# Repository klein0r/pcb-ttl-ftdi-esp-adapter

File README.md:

# TTL over RJ10 to FTDI/ESP12 PCB

[Gerber-Files](https://github.com/klein0r/pcb-ttl-ftdi-esp-adapter/releases)

## Preview

## License

The MIT License (MIT)

Copyright (c) 2026 Matthias Kleine <info@haus-automatisierung.com>

Permission is hereby granted, free of charge, to any person obtaining a copy
of this software and associated documentation files (the "Software"), to deal
in the Software without restriction, including without limitation the rights
to use, copy, modify, merge, publish, distribute, sublicense, and/or sell
copies of the Software, and to permit persons to whom the Software is
furnished to do so, subject to the following conditions:

The above copyright notice and this permission notice shall be included in
all copies or substantial portions of the Software.

THE SOFTWARE IS PROVIDED "AS IS", WITHOUT WARRANTY OF ANY KIND, EXPRESS OR
IMPLIED, INCLUDING BUT NOT LIMITED TO THE WARRANTIES OF MERCHANTABILITY,
FITNESS FOR A PARTICULAR PURPOSE AND NONINFRINGEMENT. IN NO EVENT SHALL THE
AUTHORS OR COPYRIGHT HOLDERS BE LIABLE FOR ANY CLAIM, DAMAGES OR OTHER
LIABILITY, WHETHER IN AN ACTION OF CONTRACT, TORT OR OTHERWISE, ARISING FROM,
OUT OF OR IN CONNECTION WITH THE SOFTWARE OR THE USE OR OTHER DEALINGS IN
THE SOFTWARE.

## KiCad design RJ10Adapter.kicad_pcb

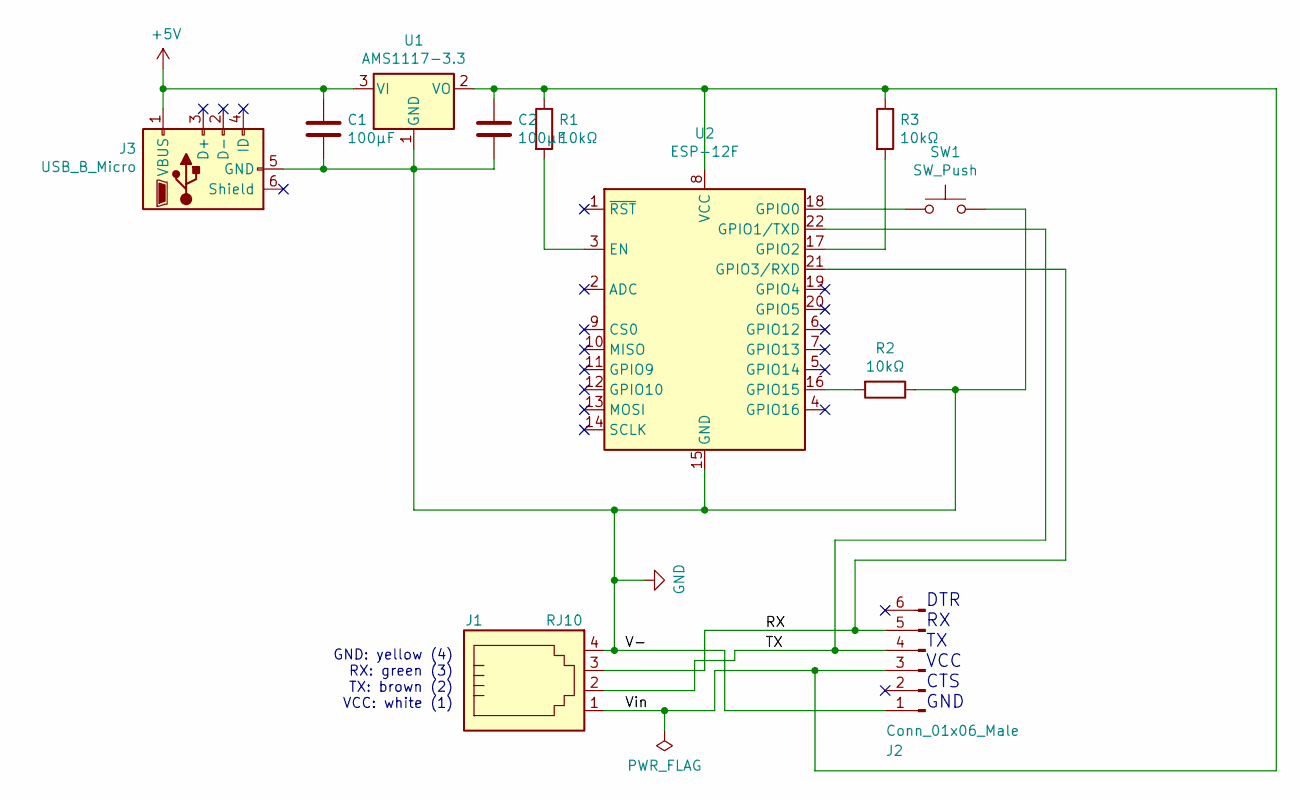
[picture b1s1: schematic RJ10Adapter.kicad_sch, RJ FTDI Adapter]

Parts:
C1, C2: 100µF; C_0805_2012Metric_Pad1.18x1.45mm_HandSolder
J1: RJ10; MEBP_44S
J2: Conn_01x06_Male; PinHeader_1x06_P2.54mm_Vertical
J3: USB_B_Micro; USB_Micro-B_Molex_47346-0001
R1, R2, R3: 10kΩ; R_0805_2012Metric_Pad1.20x1.40mm_HandSolder
SW1: SW_Push; SW_SPST_CK_RS282G05A3
U1: AMS1117-3.3; SOT-223-3_TabPin2
U2: ESP-12F; ESP-12E

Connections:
+5V: C1.1, J3.1 (VBUS), U1.3 (VI)
/RX: J1.3, J2.5, U2.21 (GPIO3/RXD)
/TX: J1.2, J2.4, U2.22 (GPIO1/TXD)
/Vin: C2.1, J1.1, J2.3, R1.1, R3.1, U1.2 (VO), U2.8 (VCC)
GND: C1.2, C2.2, J1.4, J2.1, J3.5 (GND), R2.1, SW1.2, U1.1 (GND), U2.15 (GND)
unnamed: R1.2, U2.3 (EN)
unnamed: SW1.1, U2.18 (GPIO0)
unnamed: R3.2, U2.17 (GPIO2)
unnamed: R2.2, U2.16 (GPIO15)

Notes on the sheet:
GND: yellow (4) RX: green (3) TX: brown (2) VCC: white (1)
DTR RX TX VCC CTS GND

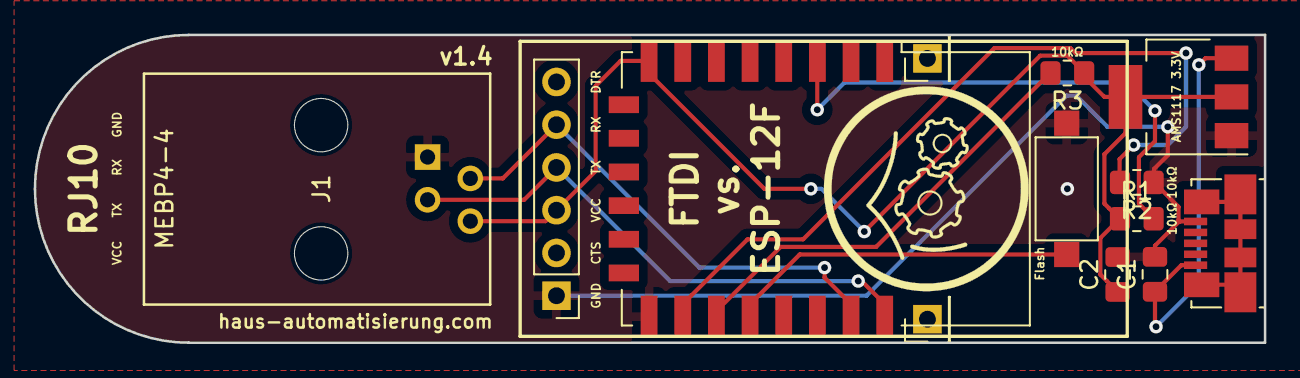
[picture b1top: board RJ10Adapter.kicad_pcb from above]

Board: 2 copper layers, 73.1 x 18.3 mm, 11 parts (0 on the bottom side), 9 nets.

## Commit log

2019-05-01 Resistor to GPIO
2019-05-18 added resistor
2019-10-24 Added 10k resistor
2020-08-09 Changed RX and TX
2021-09-25 Readme and minor changes
2021-10-13 Preview Photo
2022-01-30 Update LICENSE
2022-01-30 Updated to KiCad 6
2022-01-30 Deleted unconnected tracks
2024-03-15 v1.4
2026-01-28 chore: update year to 2026 in LICENSE and README
2026-01-28 Year 2026
2026-01-28 Year 2026
    Update copyright year in the README file
